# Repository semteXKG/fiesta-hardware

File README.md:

`idf.py.exe -p COM4 -DPRIMARY=1 -DFORD=1 build flash monitor`

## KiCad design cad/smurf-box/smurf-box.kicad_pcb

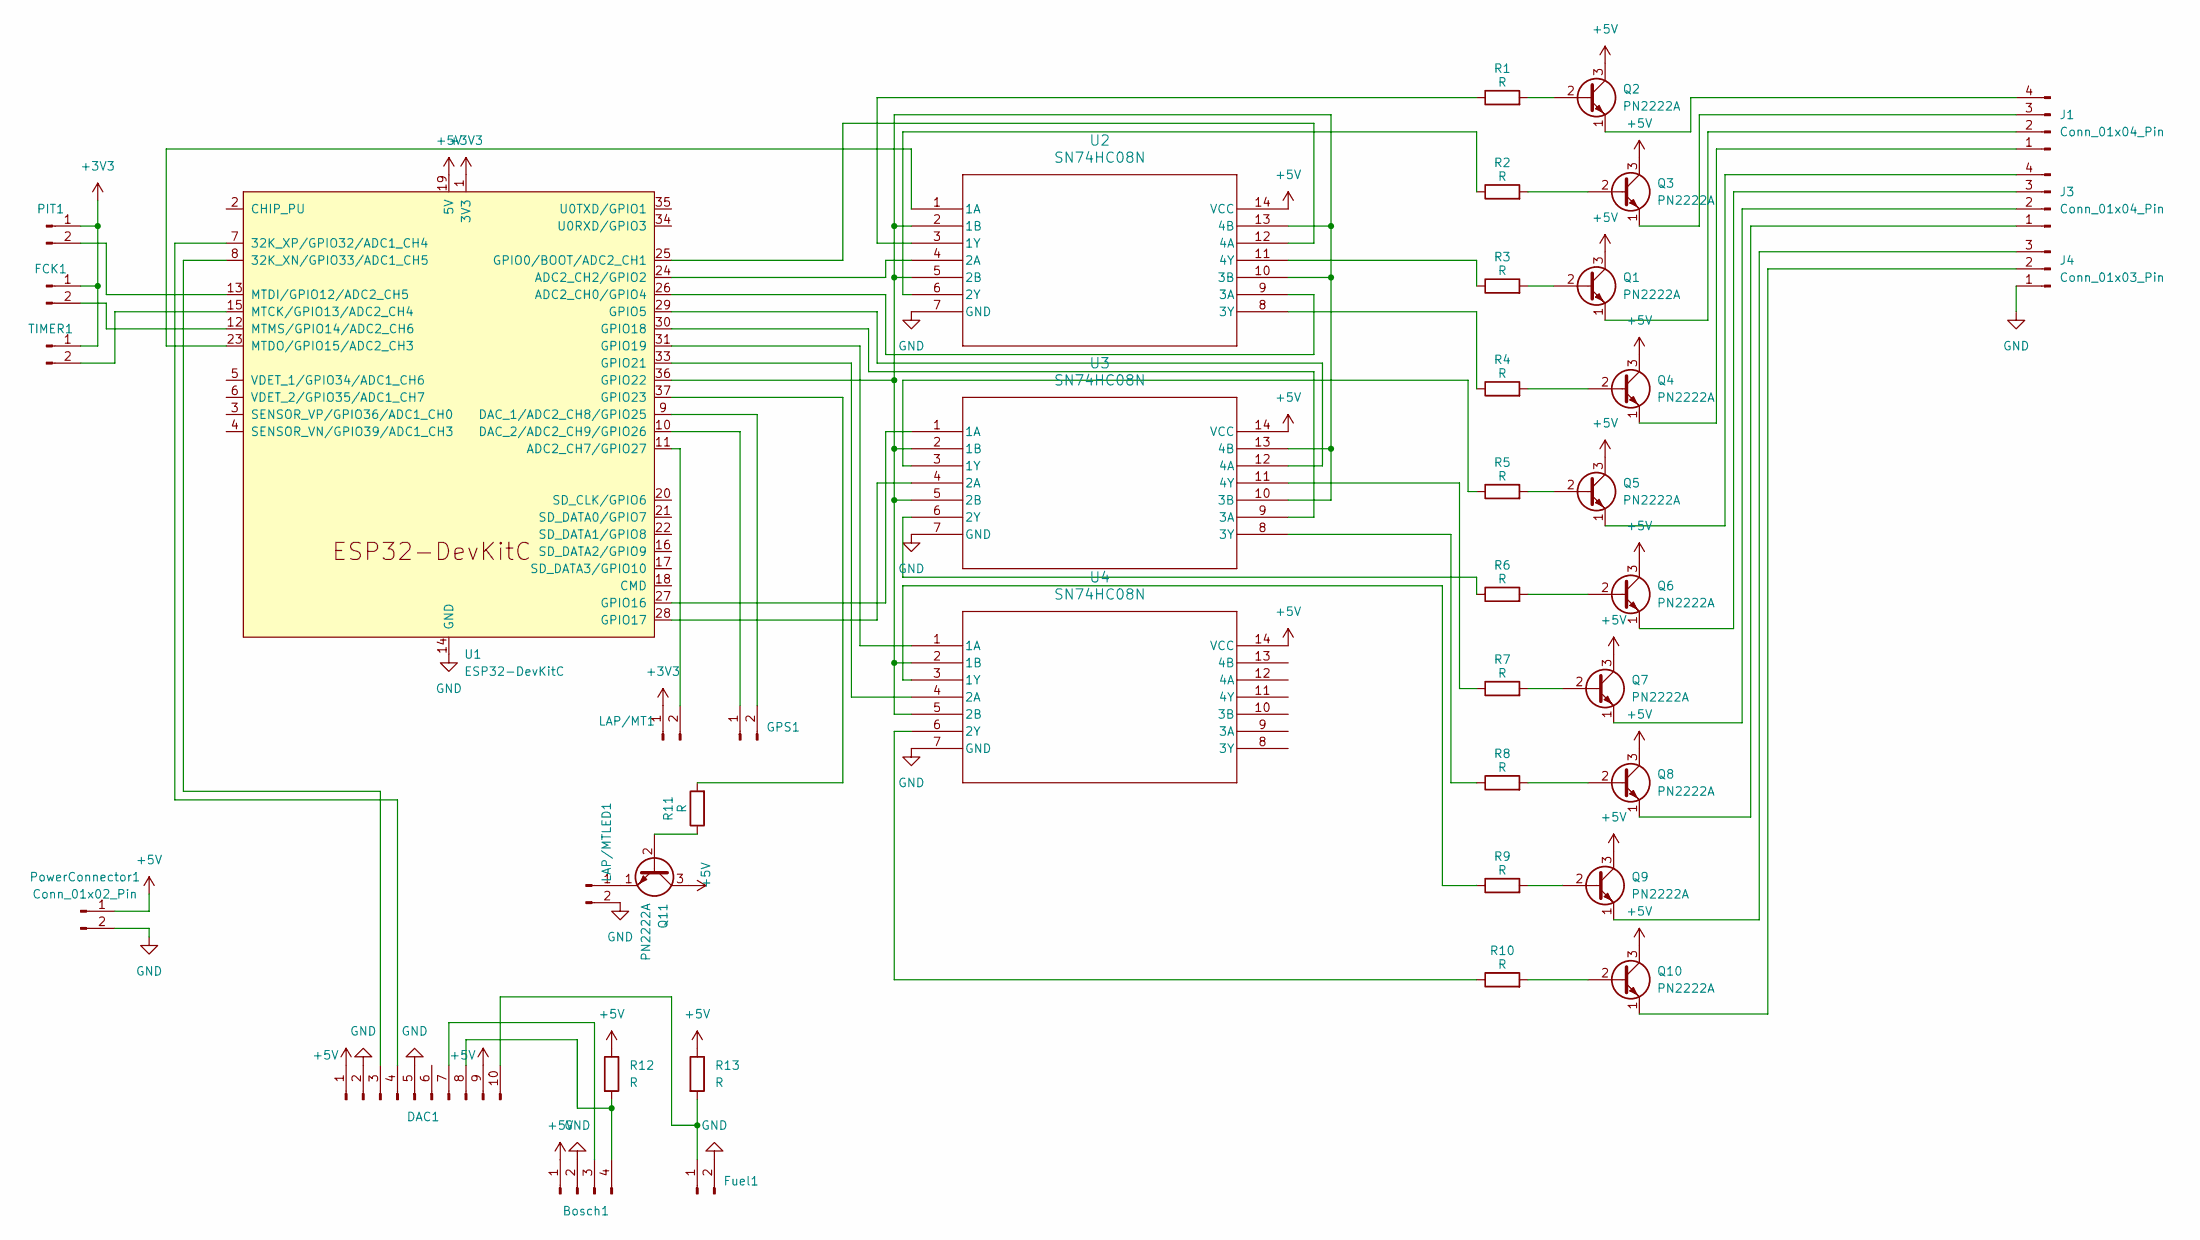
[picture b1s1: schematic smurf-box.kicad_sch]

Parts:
Bosch1: Conn_01x04_Pin; JST_XH_B4B-XH-A_1x04_P2.50mm_Vertical
DAC1: PinSocket_1x10_P2.54mm_Vertical
FCK1: Conn_01x02_Pin; JST_XH_B2B-XH-A_1x02_P2.50mm_Vertical
Fuel1: Conn_01x02_Pin; JST_XH_B2B-XH-A_1x02_P2.50mm_Vertical
GPS1: Conn_01x02_Pin; JST_XH_B2B-XH-A_1x02_P2.50mm_Vertical
J1, J3: Conn_01x04_Pin; JST_XH_B4B-XH-A_1x04_P2.50mm_Vertical
J4: Conn_01x03_Pin; JST_XH_B3B-XH-A_1x03_P2.50mm_Vertical
LAP/MT1: Conn_01x02_Pin; JST_XH_B2B-XH-A_1x02_P2.50mm_Vertical
LAP/MTLED1: Conn_01x02_Pin; JST_XH_B2B-XH-A_1x02_P2.50mm_Vertical
PIT1: Conn_01x02_Pin; JST_XH_B2B-XH-A_1x02_P2.50mm_Vertical
PowerConnector1: Conn_01x02_Pin; JST_XH_B2B-XH-A_1x02_P2.50mm_Vertical
Q1, Q2, Q3, Q4, Q5, Q6, Q7, Q8, Q9, Q10, Q11: PN2222A; TO-92_Inline
R1, R2, R3, R4, R5, R6, R7, R8, R9, R10, R11, R12, R13: R; R_Axial_DIN0207_L6.3mm_D2.5mm_P10.16mm_Horizontal
TIMER1: Conn_01x02_Pin; JST_XH_B2B-XH-A_1x02_P2.50mm_Vertical
U1: ESP32-DevKitC
U2, U3, U4: SN74HC08N; N14

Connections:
+3V3: FCK1.1, LAP/MT1.1, PIT1.1, TIMER1.1, U1.1 (3V3)
+5V: Bosch1.1, DAC1.1, DAC1.9, PowerConnector1.1, Q1.3 (C), Q2.3 (C), Q3.3 (C), Q4.3 (C), Q5.3 (C), Q6.3 (C), Q7.3 (C), Q8.3 (C), Q9.3 (C), Q10.3 (C), Q11.3 (C), R12.1, R13.1, U1.19 (5V), U2.14 (VCC), U3.14 (VCC), U4.14 (VCC)
GND: Bosch1.2, DAC1.2, DAC1.5, Fuel1.2, J4.1, LAP/MTLED1.2, PowerConnector1.2, U1.14 (GND), U1.32 (GND), U1.38 (GND), U2.7 (GND), U3.7 (GND), U4.7 (GND)
unnamed: Bosch1.3, DAC1.7
unnamed: Bosch1.4, DAC1.8, R12.2
unnamed: DAC1.3, U1.8 (32K_XN/GPIO33/ADC1_CH5)
unnamed: DAC1.4, U1.7 (32K_XP/GPIO32/ADC1_CH4)
unnamed: DAC1.10, Fuel1.1, R13.2
unnamed: FCK1.2, U1.12 (MTMS/GPIO14/ADC2_CH6)
unnamed: GPS1.1, U1.10 (DAC_2/ADC2_CH9/GPIO26)
unnamed: GPS1.2, U1.9 (DAC_1/ADC2_CH8/GPIO25)
unnamed: J1.1, Q4.1 (E)
unnamed: J1.2, Q1.1 (E)
unnamed: J1.3, Q3.1 (E)
unnamed: J1.4, Q2.1 (E)
unnamed: J3.1, Q8.1 (E)
unnamed: J3.2, Q7.1 (E)
unnamed: J3.3, Q6.1 (E)
unnamed: J3.4, Q5.1 (E)
unnamed: J4.2, Q10.1 (E)
unnamed: J4.3, Q9.1 (E)
unnamed: LAP/MT1.2, U1.11 (ADC2_CH7/GPIO27)
unnamed: LAP/MTLED1.1, Q11.1 (E)
unnamed: PIT1.2, U1.13 (MTDI/GPIO12/ADC2_CH5)
unnamed: Q1.2 (B), R3.2
unnamed: Q2.2 (B), R1.2
unnamed: Q3.2 (B), R2.2
unnamed: Q4.2 (B), R4.2
unnamed: Q5.2 (B), R5.2
unnamed: Q6.2 (B), R6.2
unnamed: Q7.2 (B), R7.2
unnamed: Q8.2 (B), R8.2
unnamed: Q9.2 (B), R9.2
unnamed: Q10.2 (B), R10.2
unnamed: Q11.2 (B), R11.1
unnamed: TIMER1.2, U1.15 (MTCK/GPIO13/ADC2_CH4)
unnamed: U1.26 (ADC2_CH0/GPIO4), U2.9 (3A)
unnamed: U1.24 (ADC2_CH2/GPIO2), U2.4 (2A)
unnamed: U1.25 (GPIO0/BOOT/ADC2_CH1), U2.12 (4A)
unnamed: U1.29 (GPIO5), U3.12 (4A)
unnamed: U1.27 (GPIO16), U3.1 (1A)
unnamed: U1.28 (GPIO17), U3.4 (2A)
unnamed: U1.30 (GPIO18), U3.9 (3A)
unnamed: U1.31 (GPIO19), U4.1 (1A)
unnamed: U1.33 (GPIO21), U4.4 (2A)
unnamed: U1.36 (GPIO22), U2.2 (1B), U2.5 (2B), U2.10 (3B), U2.13 (4B), U3.2 (1B), U3.5 (2B), U3.10 (3B), U3.13 (4B), U4.2 (1B), U4.5 (2B)
unnamed: R11.2, U1.37 (GPIO23)
unnamed: U1.23 (MTDO/GPIO15/ADC2_CH3), U2.1 (1A)
unnamed: R1.1, U2.3 (1Y)
unnamed: R2.1, U2.6 (2Y)
unnamed: R4.1, U2.8 (3Y)
unnamed: R3.1, U2.11 (4Y)
unnamed: R5.1, U3.3 (1Y)
unnamed: R6.1, U3.6 (2Y)
unnamed: R8.1, U3.8 (3Y)
unnamed: R7.1, U3.11 (4Y)
unnamed: R9.1, U4.3 (1Y)
unnamed: R10.1, U4.6 (2Y)

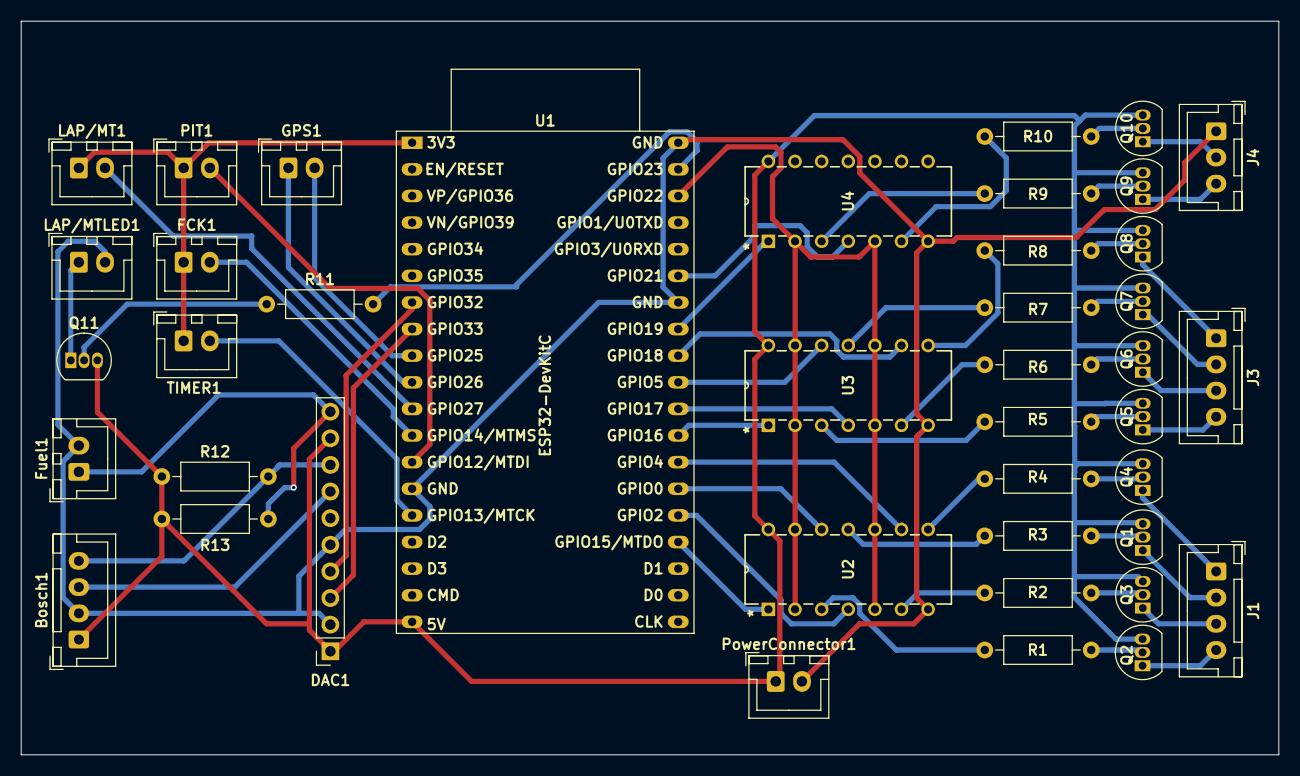
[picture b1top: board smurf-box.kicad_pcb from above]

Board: 2 copper layers, 120.0 x 70.0 mm, 41 parts (0 on the bottom side), 58 nets.
